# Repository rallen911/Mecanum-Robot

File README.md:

# Mecanum-Robot
Robot with mecanum wheels driven by ESP32

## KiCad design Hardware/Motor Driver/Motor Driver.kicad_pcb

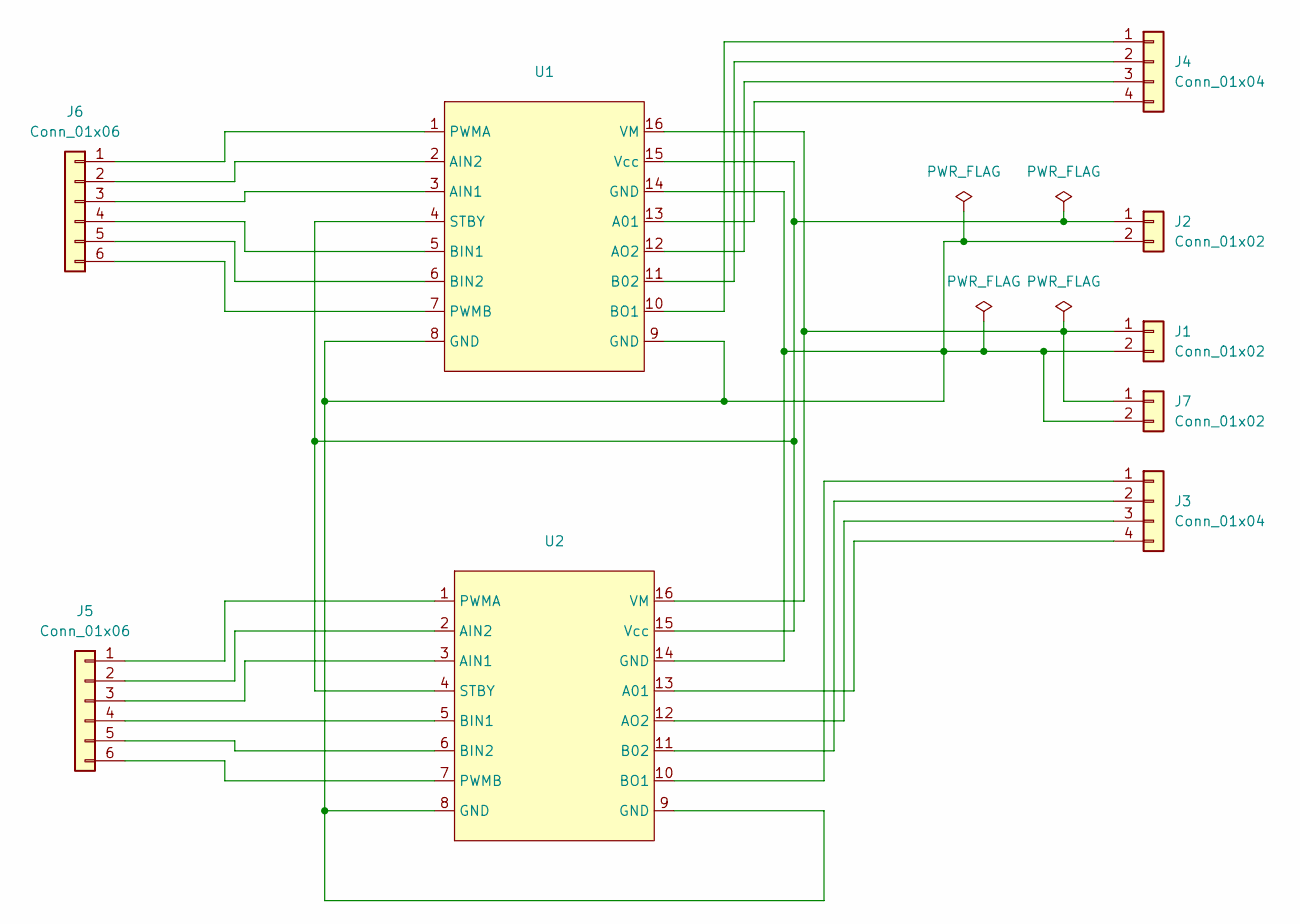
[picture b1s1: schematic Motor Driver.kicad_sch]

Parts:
J1, J2, J7: Conn_01x02; JST_XH_B2B-XH-A_1x02_P2.50mm_Vertical
J3, J4: Conn_01x04; JST_XH_B4B-XH-A_1x04_P2.50mm_Vertical
J5, J6: Conn_01x06; JST_XH_B6B-XH-A_1x06_P2.50mm_Vertical
U1, U2: TB6612FNG Module_2x08_P2.54_W15.24mm

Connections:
unnamed: J1.1, J7.1, U1.16 (VM), U2.16 (VM)
unnamed: J1.2, J2.2, J7.2, U1.8 (GND), U1.9 (GND), U1.14 (GND), U2.8 (GND), U2.9 (GND), U2.14 (GND)
unnamed: J2.1, U1.4 (STBY), U1.15 (Vcc), U2.4 (STBY), U2.15 (Vcc)
unnamed: J3.1, U2.10 (BO1)
unnamed: J3.2, U2.11 (B02)
unnamed: J3.3, U2.12 (AO2)
unnamed: J3.4, U2.13 (A01)
unnamed: J4.1, U1.10 (BO1)
unnamed: J4.2, U1.11 (B02)
unnamed: J4.3, U1.12 (AO2)
unnamed: J4.4, U1.13 (A01)
unnamed: J5.1, U2.1 (PWMA)
unnamed: J5.2, U2.2 (AIN2)
unnamed: J5.3, U2.3 (AIN1)
unnamed: J5.4, U2.5 (BIN1)
unnamed: J5.5, U2.6 (BIN2)
unnamed: J5.6, U2.7 (PWMB)
unnamed: J6.1, U1.1 (PWMA)
unnamed: J6.2, U1.2 (AIN2)
unnamed: J6.3, U1.3 (AIN1)
unnamed: J6.4, U1.5 (BIN1)
unnamed: J6.5, U1.6 (BIN2)
unnamed: J6.6, U1.7 (PWMB)

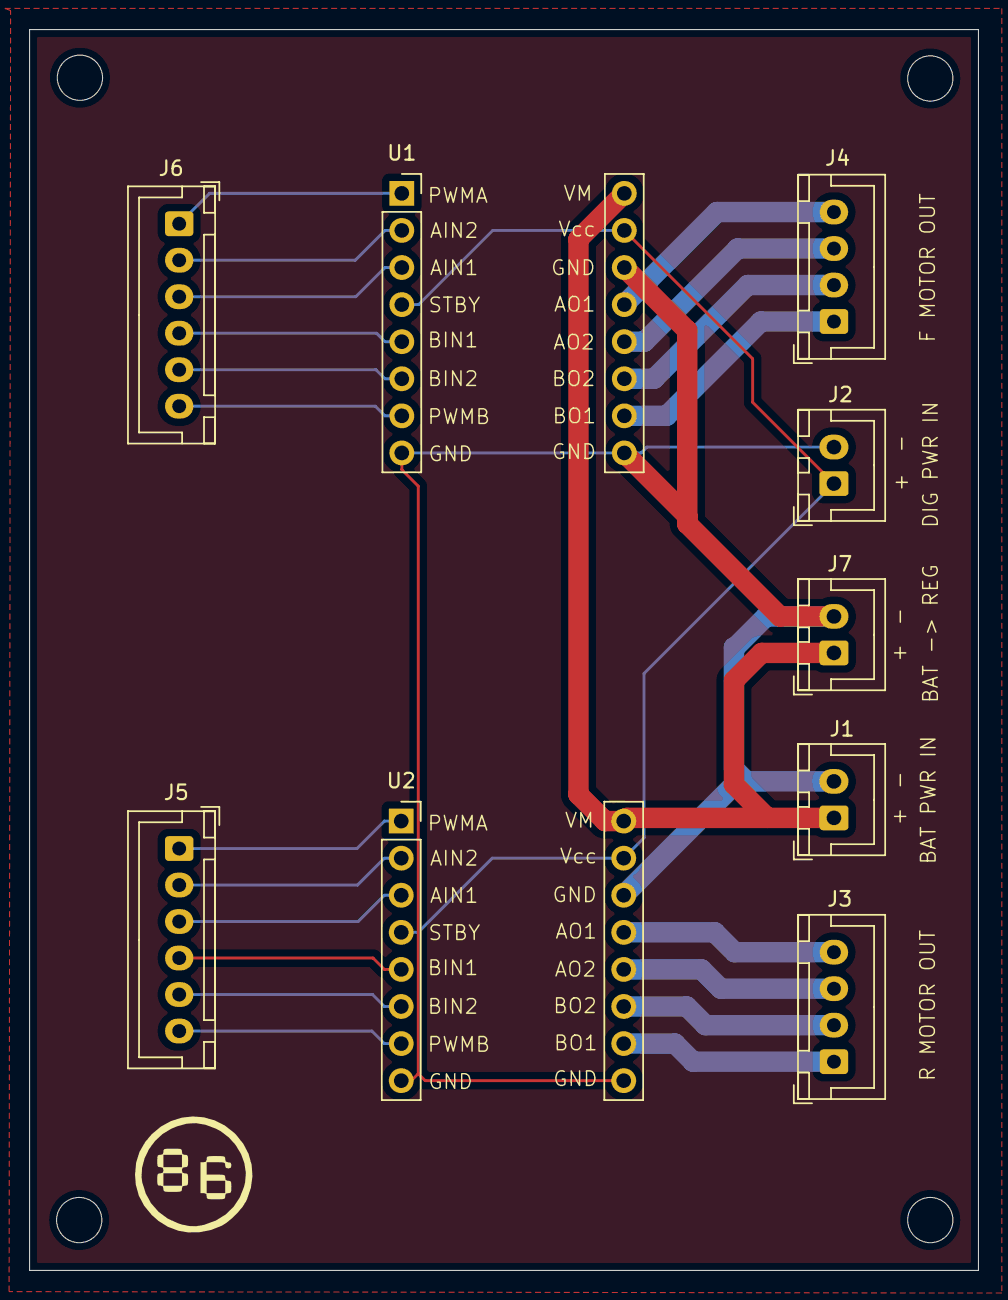
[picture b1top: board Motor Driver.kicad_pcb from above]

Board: 2 copper layers, 65.0 x 85.0 mm, 9 parts (0 on the bottom side), 23 nets.

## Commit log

2024-11-04 Initial motor driver board commit
    This commit contains the initial motor driver board design including schematic board layout.
2024-11-04 Create KiCad.gitignore
    Ignore file for KiCad projects
2024-11-04 Added .gitignore file for motor driver KiCad project
2024-11-04 Updated battery input traces on the PCB.
2024-11-04 Added 86 logo to the front silkscreen, and designed by on the back silkscreen.
2024-11-04 Fixed digital power trace routing around U2 pin 8.
2024-11-05 Connected the battery and buck converter grounds, because isolation wasn't needed in this application.
2024-11-05 Added copper fill to both sides of the board.
